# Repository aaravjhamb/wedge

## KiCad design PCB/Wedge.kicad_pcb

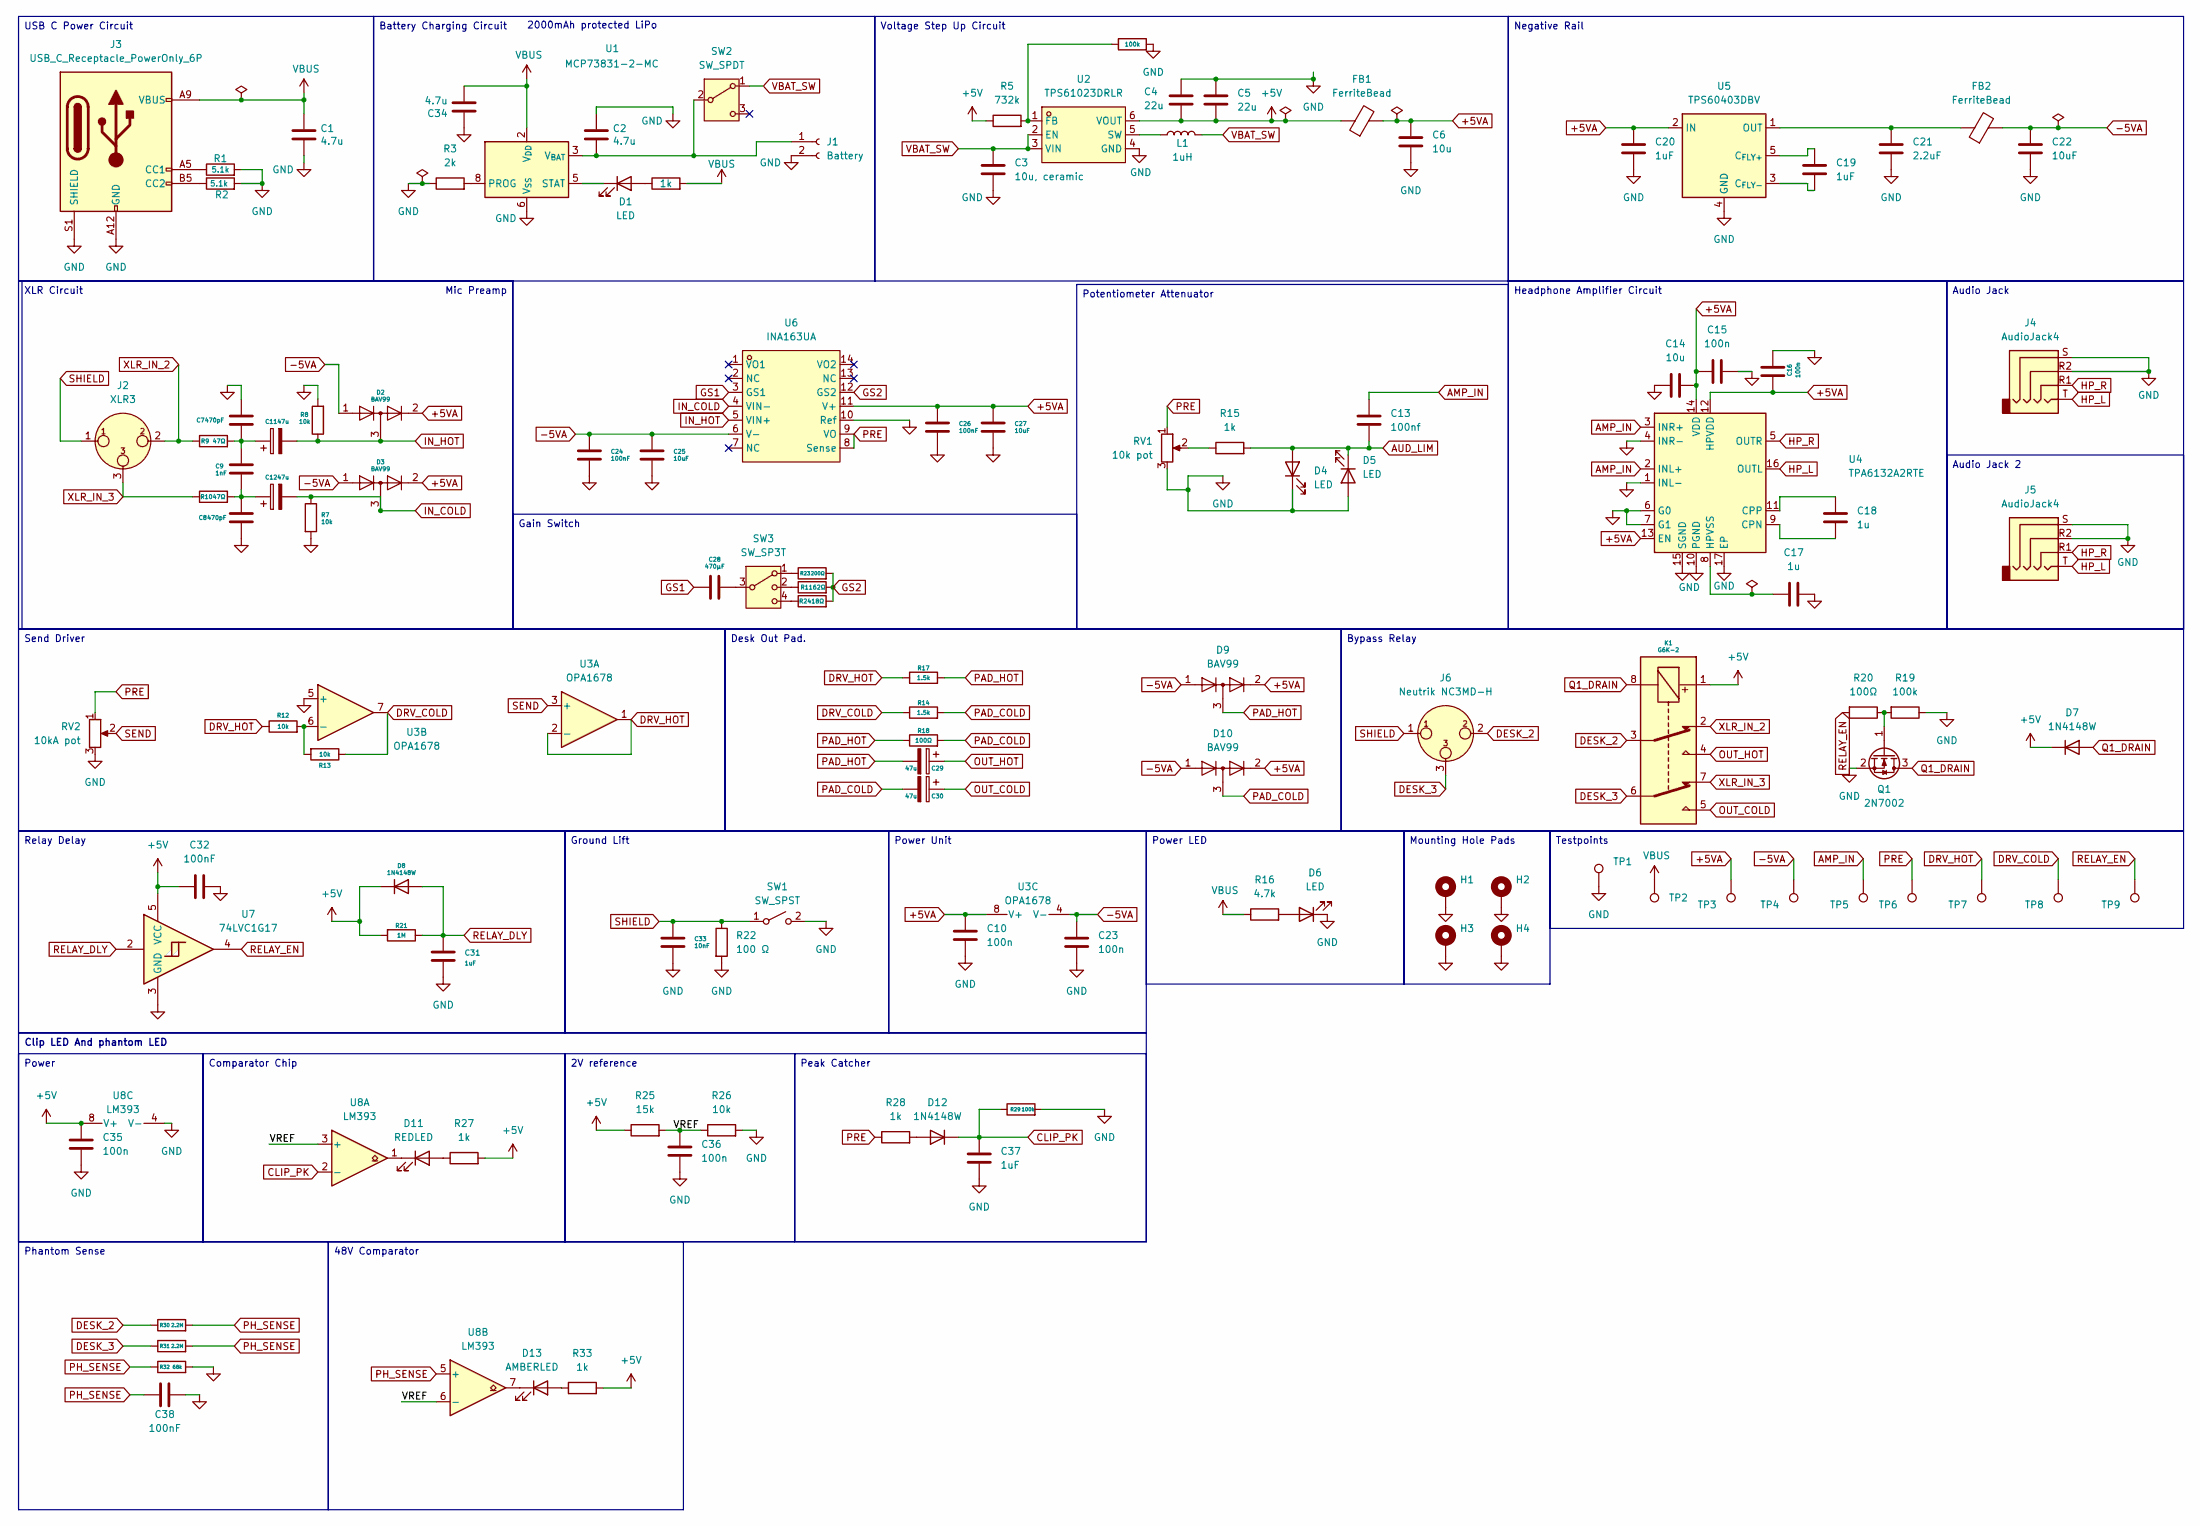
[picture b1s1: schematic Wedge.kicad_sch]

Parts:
C1, C2, C34: 4.7u; C_0603_1608Metric
C3: 10u, ceramic; C_0805_2012Metric
C4, C5: 22u; C_0805_2012Metric
C6, C14: 10u; C_0805_2012Metric
C7, C8: 470pF; C_0603_1608Metric
C9: 1nF; C_0603_1608Metric
C10, C15, C16, C23, C35, C36: 100n; C_0603_1608Metric
C11, C12, C29, C30: 47u; CP_Elec_6.3x7.7
C13: 100nf; C_0603_1608Metric
C17, C18: 1u; C_0603_1608Metric
C19, C20, C31, C37: 1uF; C_0603_1608Metric
C21: 2.2uF; C_0603_1608Metric
C22, C25, C27: 10uF; C_0805_2012Metric
C24, C26, C32, C38: 100nF; C_0603_1608Metric
C28: 470µF; CP_Elec_6.3x5.4
C33: 10nF; C_0603_1608Metric
D1, D4, D5, D6: LED; LED_0805_2012Metric
D2, D3, D9, D10: BAV99; SOT-23
D7, D8, D12: 1N4148W; D_SOD-123
D11: REDLED; LED_0805_2012Metric
D13: AMBERLED; LED_0805_2012Metric
FB1, FB2: FerriteBead; R_0805_2012Metric
H1, H2, H3, H4: MountingHole_Pad; MountingHole_2.7mm_M2.5_Pad
J1: Battery; JST_PH_B2B-PH-K_1x02_P2.00mm_Vertical
J2: XLR3; Jack_XLR_Neutrik_NC3FAAH_Horizontal
J3: USB_C_Receptacle_PowerOnly_6P; USB_C_Receptacle_HRO_TYPE-C-31-M-17
J4, J5: AudioJack4; Jack_3.5mm_PJ320D_Horizontal
J6: Neutrik NC3MD-H; Jack_XLR_Neutrik_NC3MAAH_Horizontal
K1: G6K-2; Relay_DPDT_Omron_G6K-2F-Y
L1: 1uH; L_Taiyo-Yuden_NR-40xx
Q1: 2N7002; SOT-23
R1, R2: 5.1k; R_0603_1608Metric
R3: 2k; R_0603_1608Metric
R4, R15, R27, R28, R33: 1k; R_0603_1608Metric
R5: 732k; R_0603_1608Metric
R6, R19, R29: 100k; R_0603_1608Metric
R7, R8, R12, R13, R26: 10k; R_0603_1608Metric
R9, R10: 47Ω; R_0603_1608Metric
R11: 62Ω; R_0603_1608Metric
R14, R17: 1.5k; R_0603_1608Metric
R16: 4.7k; R_0603_1608Metric
R18, R20: 100Ω; R_0603_1608Metric
R21: 1M; R_0603_1608Metric
R22: 100 Ω; R_0603_1608Metric
R23: 200Ω; R_0603_1608Metric
R24: 18Ω; R_0603_1608Metric
R25: 15k; R_0603_1608Metric
R30, R31: 2.2M; R_0603_1608Metric
R32: 68k; R_0603_1608Metric
RV1: 10k pot; Potentiometer_Bourns_PTV09A-1_Single_Vertical
RV2: 10kA pot; Potentiometer_Bourns_PTV09A-1_Single_Vertical
SW1: SW_SPST; SW_SPDT_PCM12
SW2: SW_SPDT; SW_SPDT_PCM12
SW3: SW_SP3T; SW_SP3T_G-Switch_SK-13D01-G030
TP1, TP2, TP3, TP4, TP5, TP6, TP7, TP8, TP9: TestPoint; TestPoint_Pad_D1.5mm
U1: MCP73831-2-MC; DFN-8-1EP_3x2mm_P0.5mm_EP1.7x1.4mm
U2: TPS61023DRLR; SOT-563; MPN TPS61023DRLR; LCSC Part C919459
U3: OPA1678; SOIC-8_3.9x4.9mm_P1.27mm
U4: TPA6132A2RTE; WQFN-16-1EP_3x3mm_P0.5mm_EP1.6x1.6mm_ThermalVias
U5: TPS60403DBV; SOT-23-5
U6: INA163UA; SOIC-14_L8.7-W3.9-P1.27-LS6.0-BL; MPN INA163UA; LCSC Part C2868965
U7: 74LVC1G17; SOT-23-5
U8: LM393; SOIC-8_3.9x4.9mm_P1.27mm

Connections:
+5V: C4.2, C5.2, C32.1, C35.2, D7.1 (K), D8.1 (K), FB1.1, K1.1, R5.1, R21.2, R25.1, R27.2, R33.2, U2.6 (VOUT), U7.5 (VCC), U8.8 (V+)
+5VA: C6.1, C10.2, C14.2, C15.1, C16.1, C20.2, C26.1, C27.1, D2.2 (A), D3.2 (A), D9.2 (A), D10.2 (A), FB1.2, TP3.1 (1_1), U3.8 (V+), U4.12 (HPVDD), U4.13 (EN), U4.14 (VDD), U5.2 (IN), U6.11 (V+)
-5VA: C22.1, C23.2, C24.1, C25.1, D2.1 (K), D3.1 (K), D9.1 (K), D10.1 (K), FB2.2, TP4.1 (1_1), U3.4 (V-), U6.6 (V-)
/VREF: C36.2, R25.2, R26.1, U8.3 (+), U8.6 (-)
AMP_IN: C13.1, TP5.1 (1_1), U4.2 (INL+), U4.3 (INR+)
AUD_LIM: C13.2, D4.2 (A), D5.1 (K), R15.2
CLIP_PK: C37.1, D12.1 (K), R29.1, U8.2 (-)
DESK_2: J6.2, K1.3, R30.1
DESK_3: J6.3, K1.6, R31.1
DRV_COLD: R13.1, R14.1, TP8.1 (1_1), U3.7
DRV_HOT: R12.1, R17.1, TP7.1 (1_1), U3.1, U3.2 (-)
GND: C1.2, C2.1, C3.2, C4.1, C5.1, C6.2, C7.2, C8.2, C10.1, C14.1, C15.2, C16.2, C17.1, C20.1, C21.1, C22.2, C23.1, C24.2, C25.2, C26.2, C27.2, C31.2, C32.2, C33.2, C34.1, C35.1, C36.1, C37.2, C38.2, D4.1 (K), D5.2 (A), D6.1 (K), H1.1, H2.1, H3.1, H4.1, J1.2, J3.A12 (GND), J3.B12 (GND), J3.S1 (SHIELD), J4.R2, J4.S, J5.R2, J5.S, Q1.2 (S), R1.2, R2.2, R3.1, R6.2, R7.2, R8.2, R19.1, R22.2, R26.2, R29.2, R32.2, RV1.3, RV2.3, SW1.2 (B), TP1.1 (1_1), U1.6 (V_{SS}), U2.4 (GND), U3.5 (+), U4.1 (INL-), U4.4 (INR-), U4.6 (G0), U4.7 (G1), U4.10 (PGND), U4.15 (SGND), U4.17 (EP), U5.4 (GND), U6.10 (Ref), U7.3 (GND), U8.4 (V-)
GS1: C28.1, U6.3 (GS1)
GS2: R11.2, R23.2, R24.2, U6.12 (GS2)
HP_L: J4.T, J5.T, U4.16 (OUTL)
HP_R: J4.R1, J5.R1, U4.5 (OUTR)
IN_COLD: C12.2, D3.3 (K), R7.1, U6.4 (VIN-)
IN_HOT: C11.2, D2.3 (K), R8.1, U6.5 (VIN+)
unnamed: C7.1, C9.1, C11.1, R9.2
unnamed: C8.1, C9.2, C12.1, R10.2
unnamed: C28.2, SW3.3
unnamed: D1.2 (A), R4.1
unnamed: D1.1 (K), U1.5 (STAT)
unnamed: D6.2 (A), R16.2
unnamed: D11.2 (A), R27.1
unnamed: D11.1 (K), U8.1
unnamed: D12.2 (A), R28.2
unnamed: D13.2 (A), R33.1
unnamed: D13.1 (K), U8.7
unnamed: C2.2, J1.1, SW2.2 (B), U1.3 (V_{BAT}), U1.4 (V_{BAT})
unnamed: J3.A5 (CC1), R1.1
unnamed: J3.B5 (CC2), R2.1
unnamed: Q1.1 (G), R19.2, R20.1
unnamed: R11.1, SW3.2
unnamed: R15.1, RV1.2
unnamed: R23.1, SW3.1
unnamed: R24.1, SW3.4
unnamed: R3.2, U1.8 (PROG)
unnamed: R5.2, R6.1, U2.1 (FB)
unnamed: L1.1, U2.5 (SW)
unnamed: R12.2, R13.2, U3.6 (-)
unnamed: C18.2, U4.9 (CPN)
unnamed: C18.1, U4.11 (CPP)
unnamed: C17.2, U4.8 (HPVSS)
unnamed: C19.1, U5.5 (C_{FLY+})
unnamed: C19.2, U5.3 (C_{FLY-})
unnamed: C21.2, FB2.1, U5.1 (OUT)
OUT_COLD: C30.1, K1.5
OUT_HOT: C29.1, K1.4
PAD_COLD: C30.2, D10.3 (K), R14.2, R18.2
PAD_HOT: C29.2, D9.3 (K), R17.2, R18.1
PH_SENSE: C38.1, R30.2, R31.2, R32.1, U8.5 (+)
PRE: R28.1, RV1.1, RV2.1, TP6.1 (1_1), U6.8 (Sense), U6.9 (VO)
Q1_DRAIN: D7.2 (A), K1.8, Q1.3 (D)
RELAY_DLY: C31.1, D8.2 (A), R21.1, U7.2
RELAY_EN: R20.2, TP9.1 (1_1), U7.4
SEND: RV2.2, U3.3 (+)
SHIELD: C33.1, J2.1, J6.1, R22.1, SW1.1 (A)
VBAT_SW: C3.1, L1.2, SW2.1 (A), U2.2 (EN), U2.3 (VIN)
VBUS: C1.1, C34.2, J3.A9 (VBUS), J3.B9 (VBUS), R4.2, R16.1, TP2.1 (1_1), U1.1 (V_{DD}), U1.2 (V_{DD})
XLR_IN_2: J2.2, K1.2, R9.1
XLR_IN_3: J2.3, K1.7, R10.1

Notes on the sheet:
2000mAh protected LiPo
2V reference
Peak Catcher
Potentiometer Attenuator
Testpoints
Mounting Hole Pads
48V Comparator
Voltage Step Up Circuit
Power
Battery Charging Circuit
Gain Switch
Negative Rail
Desk Out Pad.
Send Driver
Audio Jack
Headphone Amplifier Circuit
Comparator Chip
Phantom Sense
Power LED
Ground Lift
USB C Power Circuit
Bypass Relay
Audio Jack 2
Power Unit
Relay Delay
Mic Preamp
Clip LED And phantom LED
XLR Circuit

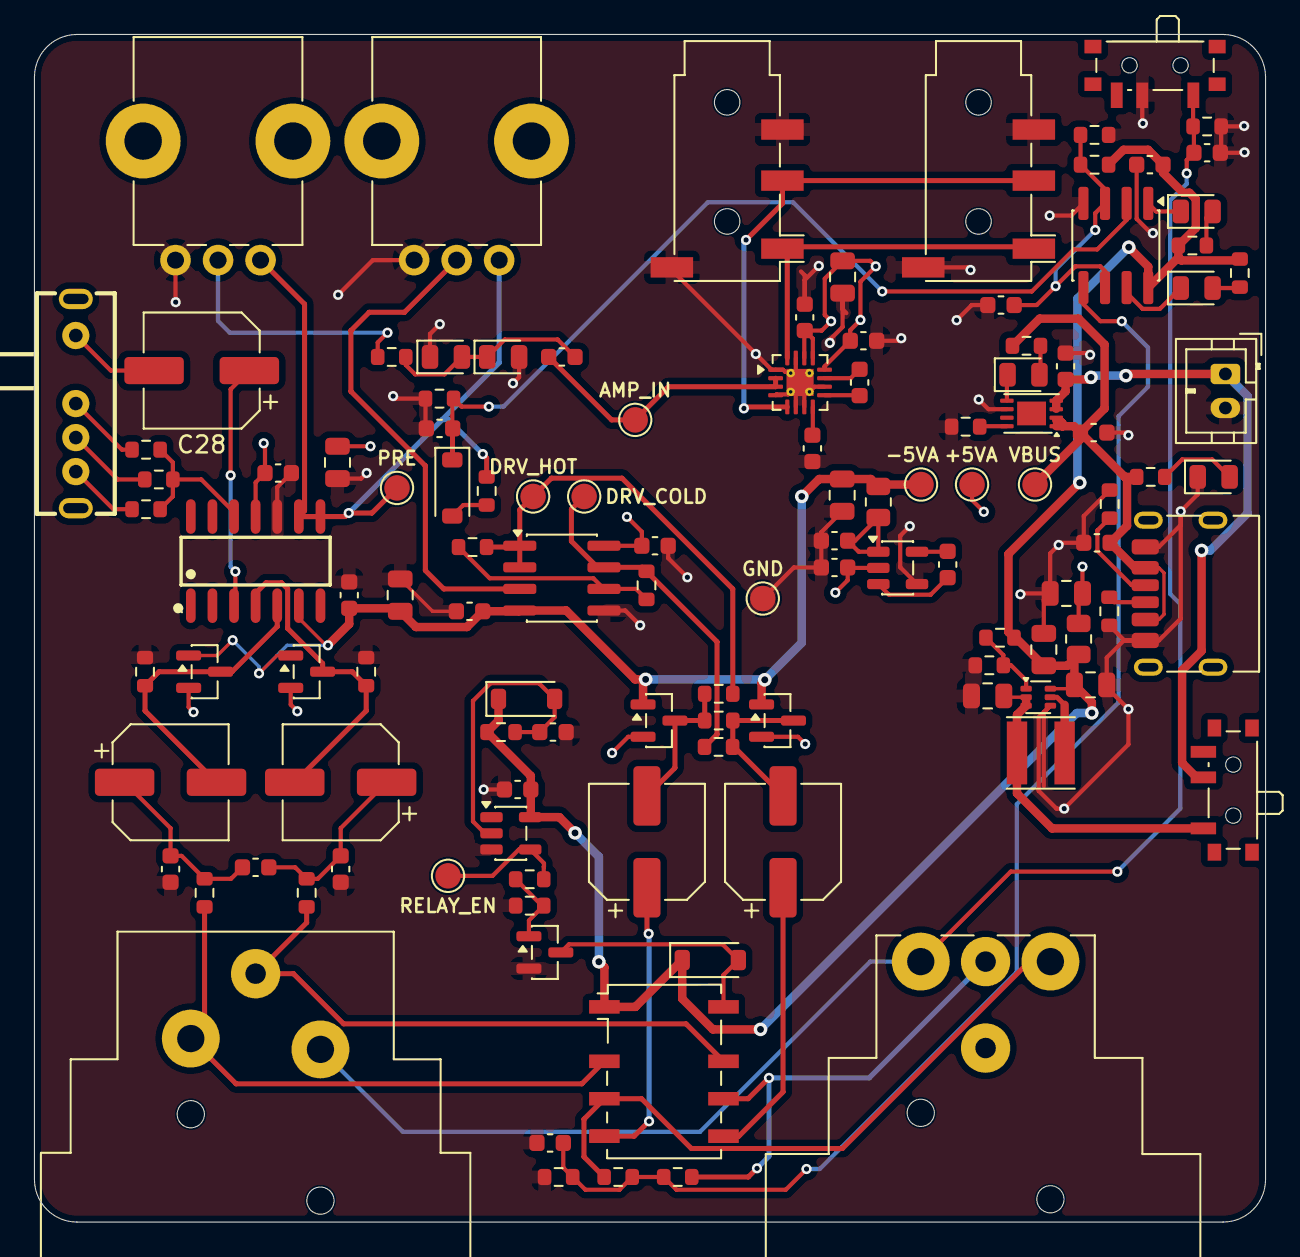
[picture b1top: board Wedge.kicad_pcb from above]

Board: 4 copper layers, 72.4 x 69.8 mm, 117 parts (0 on the bottom side), 62 nets.
